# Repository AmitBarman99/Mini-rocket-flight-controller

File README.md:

# Mini-rocket-flight-controller
PCB board of mini rocket flight controller capable to store flight data

## The image of  this PCB board :point_down:

### If you want to use this,follow these steps....

1. Download the [kicad](https://www.kicad.org/) and install it.
2. clone this repository

```bash
 git clone https://github.com/AmitBarman99/Mini-rocket-flight-controller.git 
```

3. Open the files or folder and customize them.
4. You can use [JLC pcb](https://jlcpcb.com/) for PCB fabrication

## [click here](https://amitbarman99.github.io/Mini-rocket-flight-controller/) to see the PCB board in 3D environment

 Be patient, it takes time to load
 
  I got help from this :point_right:[Repository](https://github.com/easyw/vrm360) to setup this 3D visualization. You can see it.

  ```javascript
  
  if (isAwasome){
        return true;
  }
  ```

  ## All the best

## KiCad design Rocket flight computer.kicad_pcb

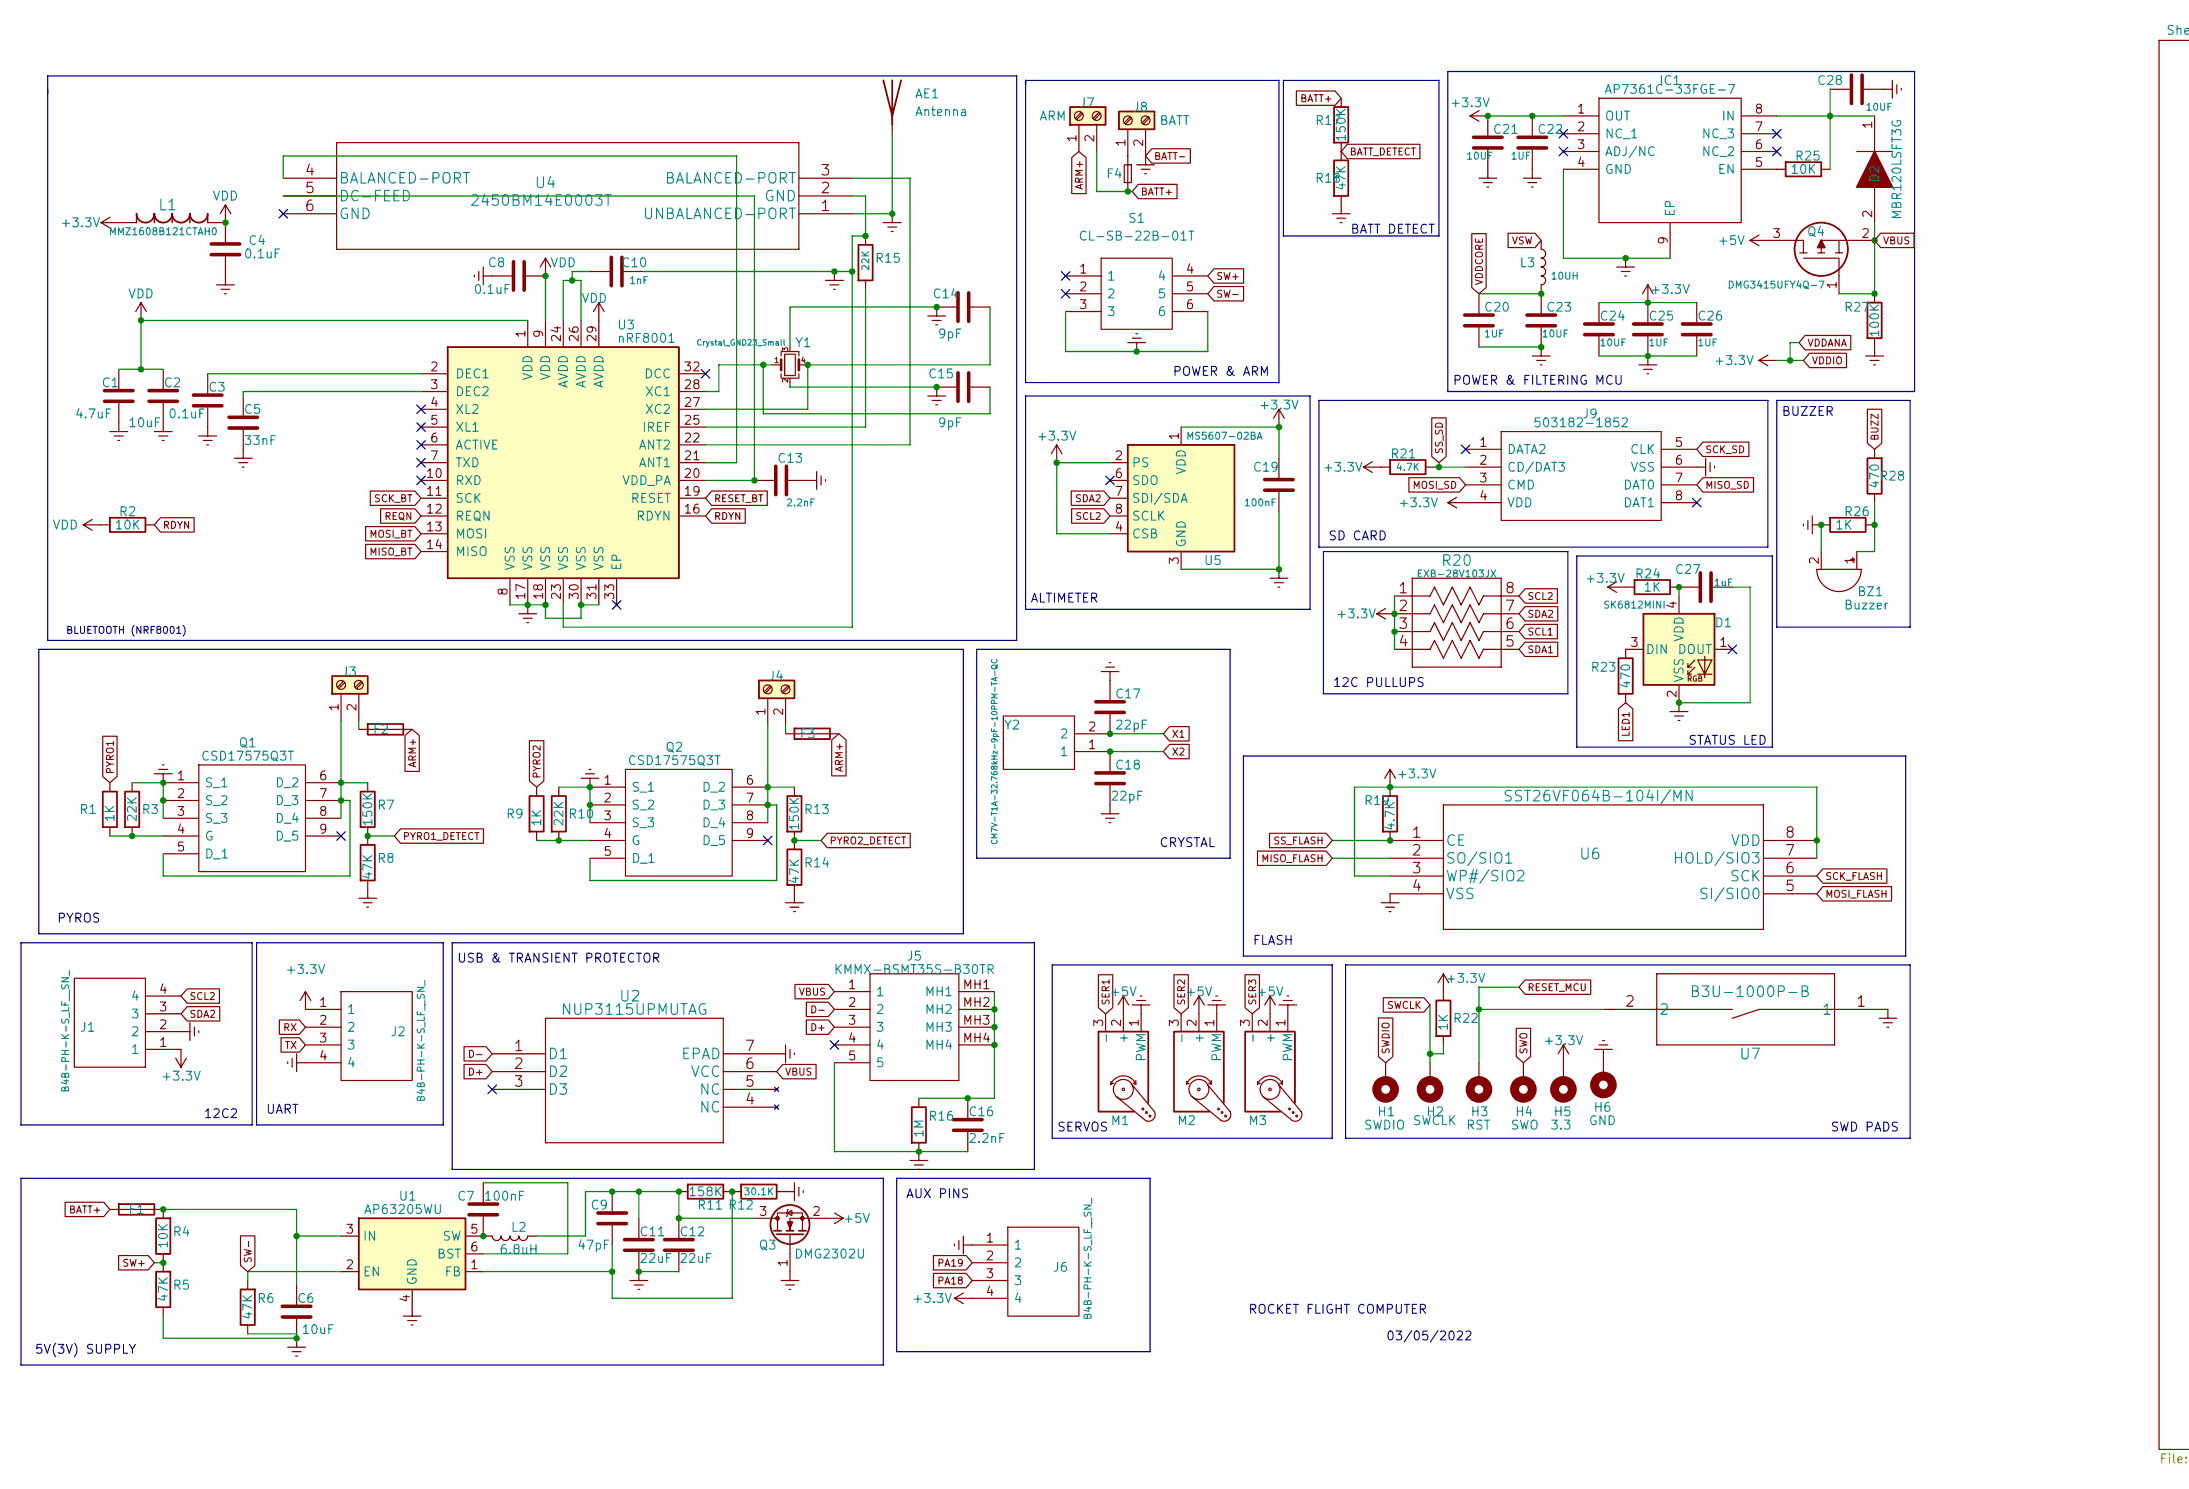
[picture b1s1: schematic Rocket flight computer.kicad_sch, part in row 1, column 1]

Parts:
AE1: Antenna; Banana_Jack_1Pin
BZ1: Buzzer; MagneticBuzzer_Kingstate_KCG0601
C1: 4.7uF; C_0201_0603Metric_Pad0.64x0.40mm_HandSolder
C2, C6: 10uF; C_0201_0603Metric_Pad0.64x0.40mm_HandSolder
C3, C4, C8: 0.1uF; C_0201_0603Metric_Pad0.64x0.40mm_HandSolder
C5: 33nF; C_0201_0603Metric_Pad0.64x0.40mm_HandSolder
C7, C19: 100nF; C_0201_0603Metric_Pad0.64x0.40mm_HandSolder
C9: 47pF; C_0201_0603Metric_Pad0.64x0.40mm_HandSolder
C10: 1nF; C_0201_0603Metric_Pad0.64x0.40mm_HandSolder
C11, C12: 22uF; C_0201_0603Metric_Pad0.64x0.40mm_HandSolder
C13, C16: 2.2nF; C_0201_0603Metric_Pad0.64x0.40mm_HandSolder
C14, C15: 9pF; C_0201_0603Metric_Pad0.64x0.40mm_HandSolder
C17, C18: 22pF; C_0201_0603Metric_Pad0.64x0.40mm_HandSolder
C20, C22, C25, C26: 1UF; C_0201_0603Metric_Pad0.64x0.40mm_HandSolder
C21, C23, C24, C28: 10UF; C_0201_0603Metric_Pad0.64x0.40mm_HandSolder
C27: 1uF; C_0201_0603Metric_Pad0.64x0.40mm_HandSolder
D1: SK6812MINI; LED_SK6812_PLCC4_5.0x5.0mm_P3.2mm
D2: MBR120LSFT3G; Manufacturer_Part_Number MBR120LSFT3G; Mouser Part Number 863-MBR120LSFT3G
F1, F2, F3: Fuse; Fuse_0402_1005Metric_Pad0.77x0.64mm_HandSolder
F4: Fuse_Small; SMA_Amphenol_132134-11_Vertical
H1: SWDIO; MountingHole_2.2mm_M2_Pad_Via
H2: SWCLK; MountingHole_2.2mm_M2_Pad_Via
H3: RST; MountingHole_2.2mm_M2_Pad_Via
H4: SWO; MountingHole_2.2mm_M2_Pad_Via
H5: 3.3; MountingHole_2.2mm_M2_Pad_Via
H6: GND; MountingHole_2.2mm_M2_Pad_Via
IC1: AP7361C-33FGE-7; Manufacturer_Part_Number AP7361C-33FGE-7; Mouser Part Number 621-AP7361C-33FGE-7
J1, J2, J6: B4B-PH-K-S_LF__SN_; B4B-PH-K-SLF_SN; Manufacturer_Part_Number B4B-PH-K-S(LF)(SN)
J3, J4, J7: ARM; Banana_Jack_2Pin
J5: KMMX-BSMT35S-B30TR; KMMXBSMT35SB30TR; Manufacturer_Part_Number KMMX-BSMT35S-B30TR; Mouser Part Number 806-KMMXBSMT35SB30TR
J8: BATT; TerminalBlock_TE_282834-2_1x02_P2.54mm_Horizontal
J9: 503182-1852; 5031821852; Manufacturer_Part_Number 503182-1852; Mouser Part Number 538-503182-1852
L1: MMZ1608B121CTAH0
L2: 6.8uH; L_0201_0603Metric_Pad0.64x0.40mm_HandSolder
L3: 10UH; L_0201_0603Metric_Pad0.64x0.40mm_HandSolder
M1, M2, M3: Motor_Servo; PinHeader_1x03_P2.54mm_Vertical_SMD_Pin1Left
Q1, Q2: CSD17575Q3T; Manufacturer_Part_Number CSD17575Q3T; Mouser Part Number 595-CSD17575Q3T
Q3: DMG2302U; SOT-23_Handsoldering
Q4: DMG3415UFY4Q-7; DMG3415UFY47; Manufacturer_Part_Number DMG3415UFY4Q-7; Mouser Part Number 621-DMG3415UFY4Q-7
R1, R9, R22, R24, R26: 1K; R_0201_0603Metric_Pad0.64x0.40mm_HandSolder
R2, R4, R25: 10K; R_0201_0603Metric_Pad0.64x0.40mm_HandSolder
R3, R10, R15: 22K; R_0201_0603Metric_Pad0.64x0.40mm_HandSolder
R5, R6, R8, R14, R18: 47K; R_0201_0603Metric_Pad0.64x0.40mm_HandSolder
R7, R13, R17: 150K; R_0201_0603Metric_Pad0.64x0.40mm_HandSolder
R11: 158K; R_0201_0603Metric_Pad0.64x0.40mm_HandSolder
R12: 30.1K; R_0201_0603Metric_Pad0.64x0.40mm_HandSolder
R16: 1M; R_0201_0603Metric_Pad0.64x0.40mm_HandSolder
R19, R21: 4.7K; R_0201_0603Metric_Pad0.64x0.40mm_HandSolder
R20: EXB-28V103JX
R23, R28: 470; R_0201_0603Metric_Pad0.64x0.40mm_HandSolder
R27: 100K; R_0201_0603Metric_Pad0.64x0.40mm_HandSolder
S1: CL-SB-22B-01T; CLSB22B01T; Manufacturer_Part_Number CL-SB-22B-01T
U1: AP63205WU; TSOT-23-6_HandSoldering
U2: NUP3115UPMUTAG
U3: nRF8001; QFN-32-1EP_5x5mm_P0.5mm_EP3.45x3.45mm
U4: 2450BM14E0003T
U5: MS5607-02BA; LGA-8_3x5mm_P1.25mm
U6: SST26VF064B-104I/MN; SST26VF064B-104IMN
U7: B3U-1000P-B
Y1: Crystal_GND23_Small; Crystal_SMD_2016-4Pin_2.0x1.6mm
Y2: CM7V-T1A-32.768kHz-9pF-10PPM-TA-QC; CM7V32768TBQA020; Manufacturer_Part_Number CM7V-T1A-32.768kHz-9pF-10PPM-TA-QC; Mouser Part Number 428-201565-MG01

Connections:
+5V: M1.2 (+), M2.2 (+), M3.2 (+), Q3.2 (S), Q4.3; also elsewhere on the board
ARM+: F2.1, F3.1, J7.1
BATT+: F1.2, F4.2, J7.2, R17.1
BATT-: AE1.1 (A), BZ1.2 (+), C1.2, C2.2, C3.2, C4.2, C5.2, C6.2, C8.2, C10.1, C11.2, C12.2, C13.1, C14.2, C15.2, C16.2, C17.1, C18.2, C19.2, C20.2, C21.2, C22.2, C23.2, C24.2, C25.2, C26.2, C27.1, C28.1, D1.2 (VSS), H6.1, IC1.4 (GND), IC1.9 (EP), J1.2, J2.4, J5.5, J6.1, J8.2, J9.6 (VSS), M1.1 (PWM), M2.1 (PWM), M3.1 (PWM), Q1.1 (S_1), Q1.2 (S_2), Q1.3 (S_3), Q2.1 (S_1), Q2.2 (S_2), Q2.3 (S_3), Q3.1 (G), R3.1, R5.1, R6.1, R8.2, R10.1, R12.1, R14.2, R15.1, R16.2, R18.2, R26.2, R27.2, S1.3, S1.6, U1.4 (GND), U2.7 (EPAD), U3.8 (VSS), U3.17 (VSS), U3.18 (VSS), U3.23 (VSS), U3.30 (VSS), U3.31 (VSS), U4.1 (UNBALANCED-PORT), U4.2 (GND), U5.3 (GND), U6.4 (VSS), U7.1, Y1.2, Y1.3; also elsewhere on the board
BATT_DETECT: R17.2, R18.1; also elsewhere on the board
BUZZ: R28.2; also elsewhere on the board
D+: J5.3, U2.2 (D2); also elsewhere on the board
D-: J5.2, U2.1 (D1); also elsewhere on the board
LED1: R23.2; also elsewhere on the board
MISO_BT: U3.14 (MISO); also elsewhere on the board
MISO_FLASH: U6.2 (SO/SIO1); also elsewhere on the board
MISO_SD: J9.7 (DAT0); also elsewhere on the board
MOSI_BT: U3.13 (MOSI); also elsewhere on the board
MOSI_FLASH: U6.5 (SI/SIO0); also elsewhere on the board
MOSI_SD: J9.3 (CMD); also elsewhere on the board
unnamed: BZ1.1 (-), R26.1, R28.1
unnamed: C3.1, U3.2 (DEC1)
unnamed: C5.1, U3.3 (DEC2)
unnamed: C6.1, F1.1, R4.2, U1.3 (IN)
unnamed: C7.1, U1.6 (BST)
unnamed: C7.2, L2.2, U1.5 (SW)
unnamed: C9.2, R11.1, R12.2, U1.1 (FB)
unnamed: C10.2, U3.24 (AVDD), U3.26 (AVDD)
unnamed: C9.1, C11.1, C12.1, L2.1, Q3.3 (D), R11.2
unnamed: C13.2, U3.20 (VDD_PA), U4.5 (DC-FEED)
unnamed: C14.1, U3.27 (XC2), Y1.4
unnamed: C15.1, U3.28 (XC1), Y1.1
unnamed: C16.1, J5.MH1, J5.MH2, J5.MH3, J5.MH4, R16.1
unnamed: C27.2, D1.4 (VDD), R24.1
unnamed: C28.2, D2.1, IC1.8 (IN), R25.1
unnamed: D1.3 (DIN), R23.1
unnamed: F2.2, J3.2
unnamed: F3.2, J4.2
unnamed: F4.1, J8.1
unnamed: IC1.5 (EN), R25.2
unnamed: J3.1, Q1.5 (D_1), Q1.6 (D_2), Q1.7 (D_3), Q1.8 (D_4), R7.1
unnamed: J4.1, Q2.5 (D_1), Q2.6 (D_2), Q2.7 (D_3), Q2.8 (D_4), R13.1
unnamed: Q1.4 (G), R1.2, R3.2
unnamed: Q2.4 (G), R9.2, R10.2
unnamed: R15.2, U3.25 (IREF)
unnamed: U3.21 (ANT1), U4.4 (BALANCED-PORT)
unnamed: U3.22 (ANT2), U4.3 (BALANCED-PORT)
PA18: J6.3; also elsewhere on the board
PA19: J6.2; also elsewhere on the board
PYRO1: R1.1; also elsewhere on the board
PYRO1_DETECT: R7.2, R8.1; also elsewhere on the board
PYRO2: R9.1; also elsewhere on the board
PYRO2_DETECT: R13.2, R14.1; also elsewhere on the board
RDYN: R2.1, U3.16 (RDYN); also elsewhere on the board
REQN: U3.12 (REQN); also elsewhere on the board
RESET_BT: U3.19 (RESET); also elsewhere on the board
RESET_MCU: H3.1, U7.2; also elsewhere on the board
RX: J2.2; also elsewhere on the board
SCK_BT: U3.11 (SCK); also elsewhere on the board
SCK_FLASH: U6.6 (SCK); also elsewhere on the board
SCK_SD: J9.5 (CLK); also elsewhere on the board
SCL1: R20.6; also elsewhere on the board
SCL2: J1.4, R20.8, U5.8 (SCLK); also elsewhere on the board
SDA1: R20.5; also elsewhere on the board
SDA2: J1.3, R20.7, U5.7 (SDI/SDA); also elsewhere on the board
SER1: M1.3 (-); also elsewhere on the board
SER2: M2.3 (-); also elsewhere on the board
SER3: M3.3 (-); also elsewhere on the board
SS_FLASH: R19.2, U6.1 (CE); also elsewhere on the board
SS_SD: J9.2 (CD/DAT3), R21.1; also elsewhere on the board
SW+: R4.1, R5.2, S1.4
SW-: R6.2, S1.5, U1.2 (EN)
SWCLK: H2.1, R22.2; also elsewhere on the board
SWDIO: H1.1; also elsewhere on the board
SWO: H4.1; also elsewhere on the board
TX: J2.3; also elsewhere on the board
VBUS: D2.2, J5.1, Q4.1, Q4.2, R27.1, U2.6 (VCC)
VDD: C1.1, C2.1, C4.1, C8.1, L1.1, R2.2, U3.1 (VDD), U3.9 (VDD), U3.29 (AVDD)
VDDANA: C19.1, C21.1, C22.1, C24.1, C25.1, C26.1, H5.1, IC1.1 (OUT), J1.1, J2.1, J6.4, J9.4 (VDD), L1.2, R19.1, R20.1, R20.2, R20.3, R20.4, R21.2, R22.1, R24.2, U5.1 (VDD), U5.2 (PS), U5.4 (CSB), U5.5 (CSB), U6.3 (WP#/SIO2), U6.7 (HOLD/SIO3), U6.8 (VDD); also elsewhere on the board
VDDCORE: C20.1, C23.1, L3.2; also elsewhere on the board
VSW: L3.1; also elsewhere on the board
X1: C17.2, Y2.2; also elsewhere on the board
X2: C18.1, Y2.1; also elsewhere on the board

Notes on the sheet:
POWER & ARM
AUX PINS
FLASH
USB & TRANSIENT PROTECTOR
SWD PADS
BATT DETECT
BUZZER
SD CARD
PYROS
UART
5V(3V) SUPPLY
STATUS LED
BLUETOOTH (NRF8001)
03/05/2022
ROCKET FLIGHT COMPUTER
SERVOS
CRYSTAL
ALTIMETER
12C2
12C PULLUPS
POWER & FILTERING MCU

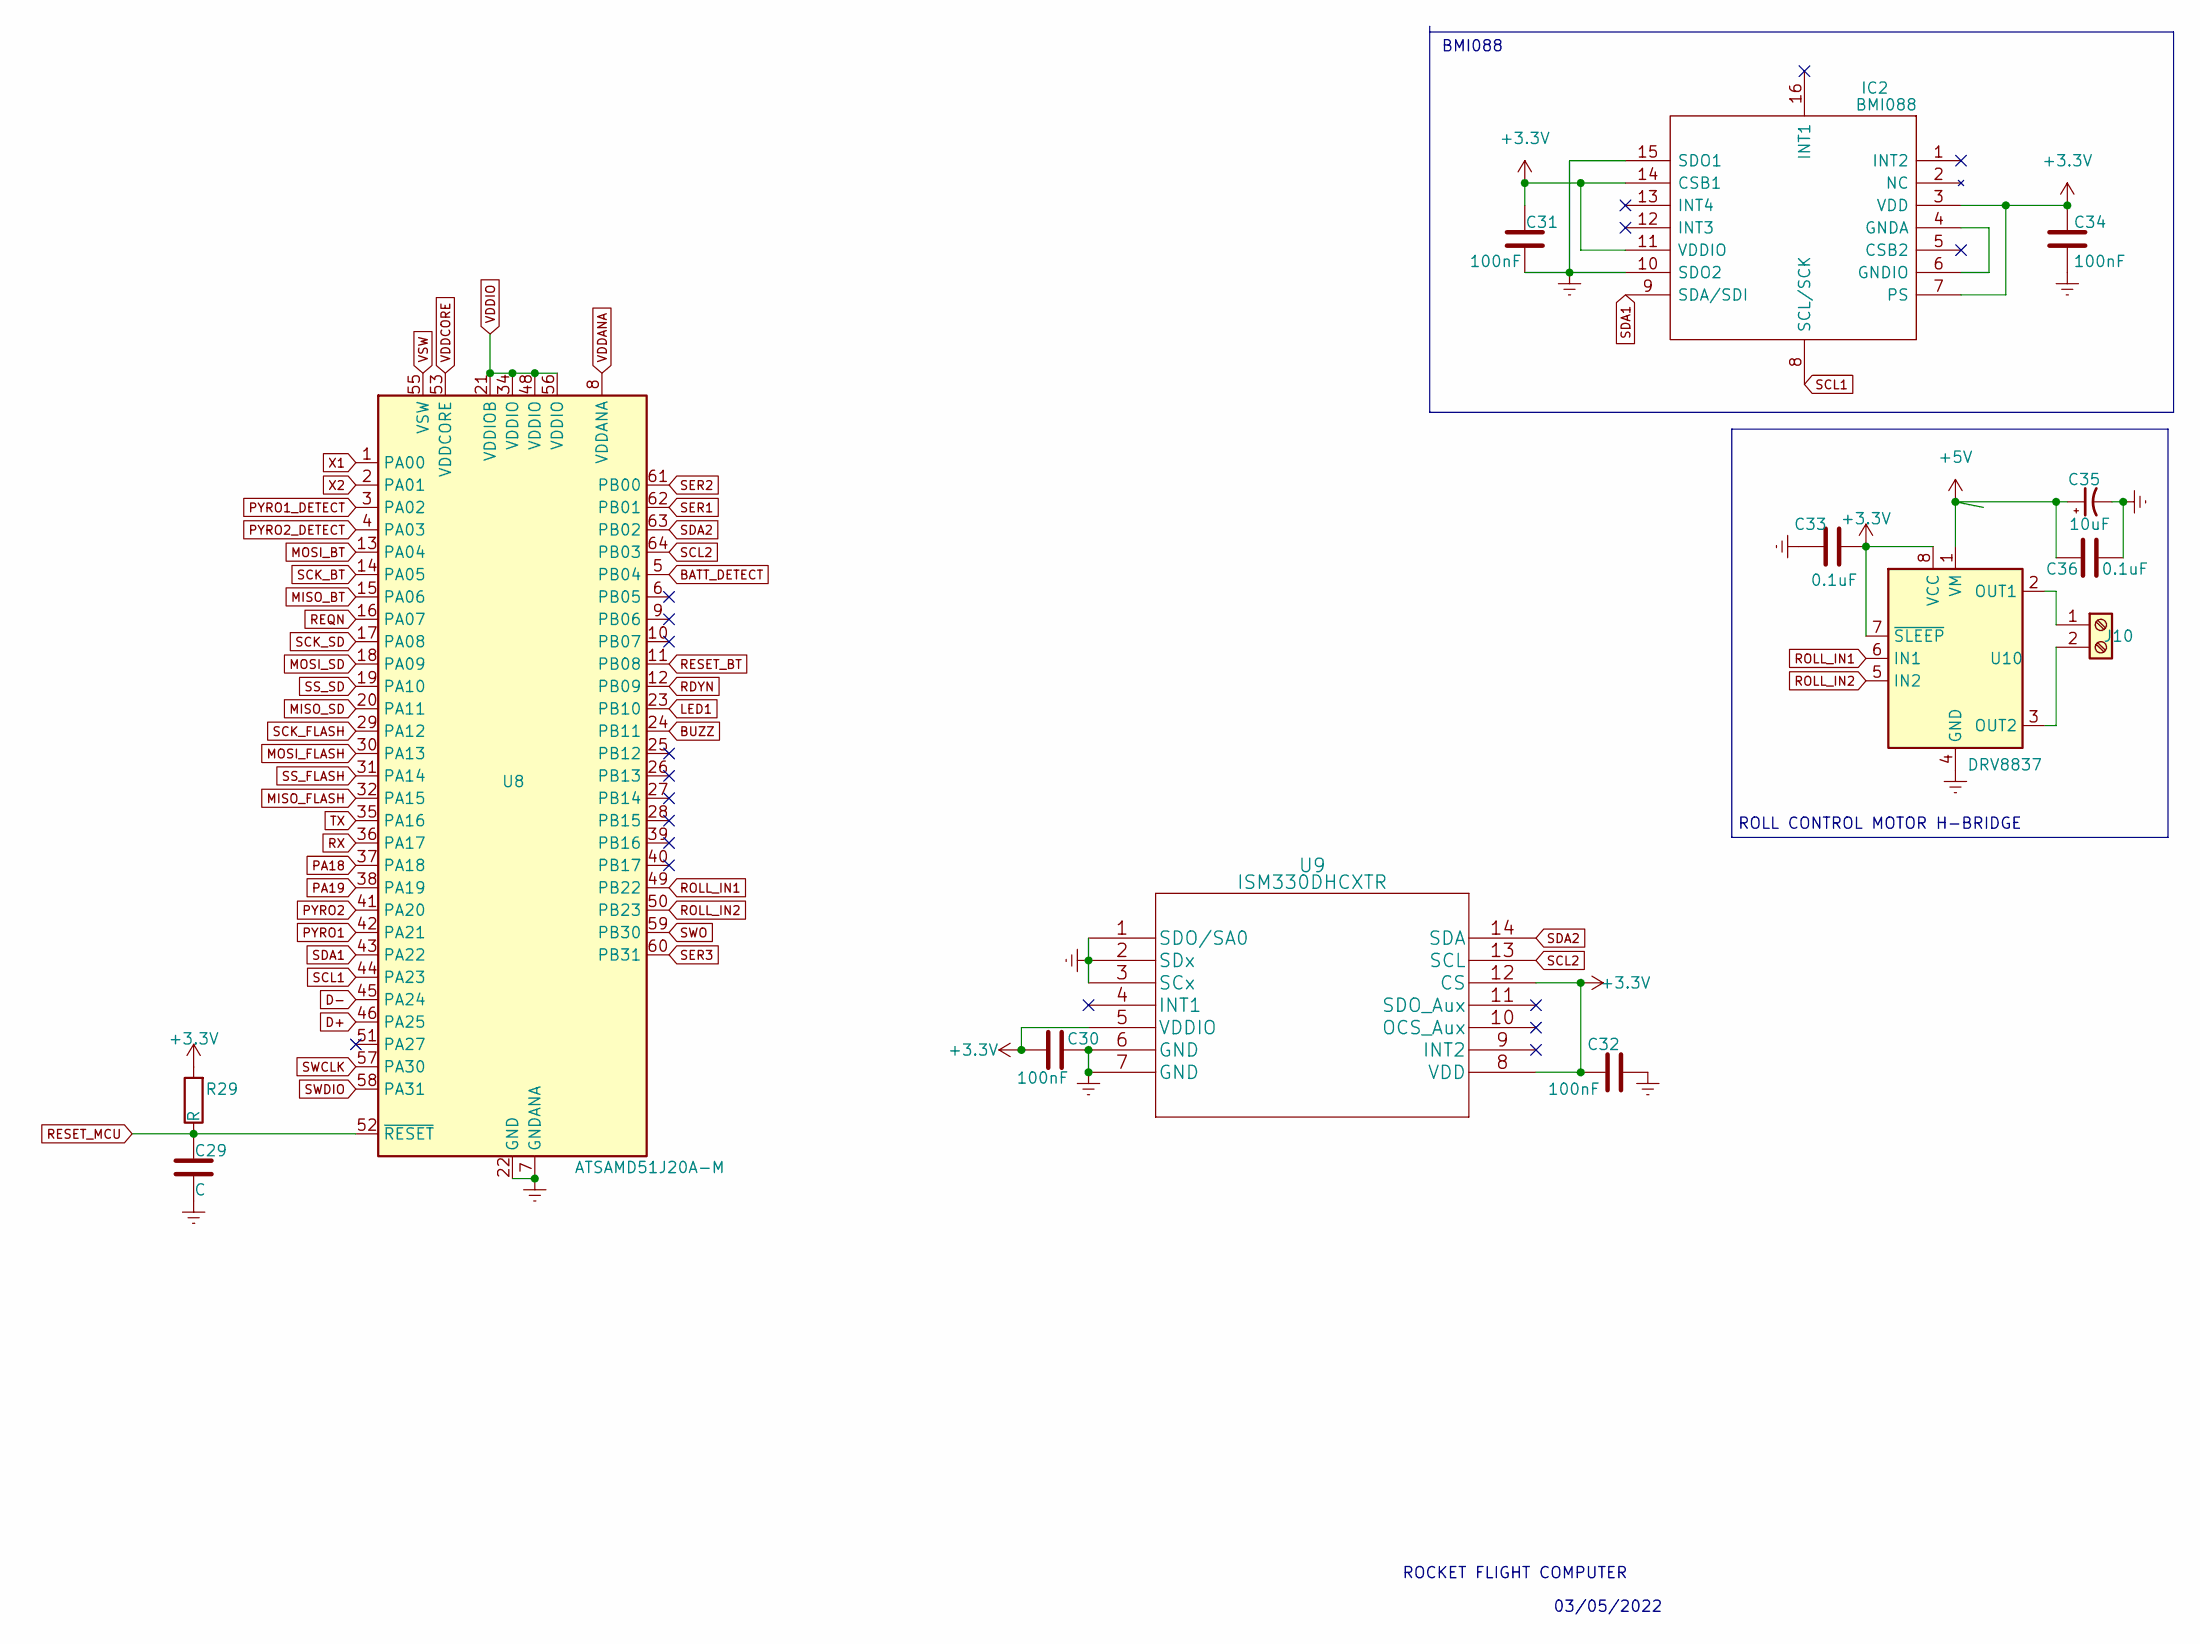
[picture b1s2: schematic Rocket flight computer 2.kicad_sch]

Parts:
C29: C; C_0201_0603Metric_Pad0.64x0.40mm_HandSolder
C30, C31, C32, C34: 100nF; C_0201_0603Metric_Pad0.64x0.40mm_HandSolder
C33, C36: 0.1uF; C_0201_0603Metric_Pad0.64x0.40mm_HandSolder
C35: 10uF; CP_EIA-1608-08_AVX-J_Pad1.25x1.05mm_HandSolder
IC2: BMI088; Manufacturer_Part_Number BMI088; Mouser Part Number 262-BMI088
J10: ARM; Banana_Jack_2Pin
R29: R; R_0201_0603Metric_Pad0.64x0.40mm_HandSolder
U8: ATSAMD51J20A-M; QFN-64-1EP_9x9mm_P0.5mm_EP3.8x3.8mm
U9: ISM330DHCXTR
U10: DRV8837; WSON-8-1EP_2x2mm_P0.5mm_EP0.9x1.6mm_ThermalVias

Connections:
+5V: C35.1, C36.2, U10.1 (VM); also elsewhere on the board
BATT-: C29.1, C30.1, C31.2, C32.1, C33.2, C34.2, C35.2, C36.1, IC2.10 (SDO2), IC2.15 (SDO1), U8.7 (GNDANA), U8.22 (GND), U8.33 (GND), U8.47 (GND), U8.54 (GND), U8.65 (GND), U9.1 (SDO/SA0), U9.2 (SDx), U9.3 (SCx), U9.6 (GND), U9.7 (GND), U10.4 (GND), U10.9 (GND); also elsewhere on the board
BATT_DETECT: U8.5 (PB04); also elsewhere on the board
BUZZ: U8.24 (PB11); also elsewhere on the board
D+: U8.46 (PA25); also elsewhere on the board
D-: U8.45 (PA24); also elsewhere on the board
LED1: U8.23 (PB10); also elsewhere on the board
MISO_BT: U8.15 (PA06); also elsewhere on the board
MISO_FLASH: U8.32 (PA15); also elsewhere on the board
MISO_SD: U8.20 (PA11); also elsewhere on the board
MOSI_BT: U8.13 (PA04); also elsewhere on the board
MOSI_FLASH: U8.30 (PA13); also elsewhere on the board
MOSI_SD: U8.18 (PA09); also elsewhere on the board
unnamed: IC2.4 (GNDA), IC2.6 (GNDIO)
unnamed: J10.1, U10.2 (OUT1)
unnamed: J10.2, U10.3 (OUT2)
PA18: U8.37 (PA18); also elsewhere on the board
PA19: U8.38 (PA19); also elsewhere on the board
PYRO1: U8.42 (PA21); also elsewhere on the board
PYRO1_DETECT: U8.3 (PA02); also elsewhere on the board
PYRO2: U8.41 (PA20); also elsewhere on the board
PYRO2_DETECT: U8.4 (PA03); also elsewhere on the board
RDYN: U8.12 (PB09); also elsewhere on the board
REQN: U8.16 (PA07); also elsewhere on the board
RESET_BT: U8.11 (PB08); also elsewhere on the board
RESET_MCU: C29.2, R29.1, U8.52 (~RESET); also elsewhere on the board
ROLL_IN1: U8.49 (PB22), U10.6 (IN1)
ROLL_IN2: U8.50 (PB23), U10.5 (IN2)
RX: U8.36 (PA17); also elsewhere on the board
SCK_BT: U8.14 (PA05); also elsewhere on the board
SCK_FLASH: U8.29 (PA12); also elsewhere on the board
SCK_SD: U8.17 (PA08); also elsewhere on the board
SCL1: IC2.8 (SCL/SCK), U8.44 (PA23); also elsewhere on the board
SCL2: U8.64 (PB03), U9.13 (SCL); also elsewhere on the board
SDA1: IC2.9 (SDA/SDI), U8.43 (PA22); also elsewhere on the board
SDA2: U8.63 (PB02), U9.14 (SDA); also elsewhere on the board
SER1: U8.62 (PB01); also elsewhere on the board
SER2: U8.61 (PB00); also elsewhere on the board
SER3: U8.60 (PB31); also elsewhere on the board
SS_FLASH: U8.31 (PA14); also elsewhere on the board
SS_SD: U8.19 (PA10); also elsewhere on the board
SWCLK: U8.57 (PA30); also elsewhere on the board
SWDIO: U8.58 (PA31); also elsewhere on the board
SWO: U8.59 (PB30); also elsewhere on the board
TX: U8.35 (PA16); also elsewhere on the board
VDDANA: C30.2, C31.1, C32.2, C33.1, C34.1, IC2.3 (VDD), IC2.7 (PS), IC2.11 (VDDIO), IC2.14 (CSB1), R29.2, U8.8 (VDDANA), U8.21 (VDDIOB), U8.34 (VDDIO), U8.48 (VDDIO), U8.56 (VDDIO), U9.5 (VDDIO), U9.8 (VDD), U9.12 (CS), U10.7 (~SLEEP), U10.8 (VCC); also elsewhere on the board
VDDCORE: U8.53 (VDDCORE); also elsewhere on the board
VSW: U8.55 (VSW); also elsewhere on the board
X1: U8.1 (PA00); also elsewhere on the board
X2: U8.2 (PA01); also elsewhere on the board

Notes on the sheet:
03/05/2022
BMI088
ROLL CONTROL MOTOR H-BRIDGE
ROCKET FLIGHT COMPUTER

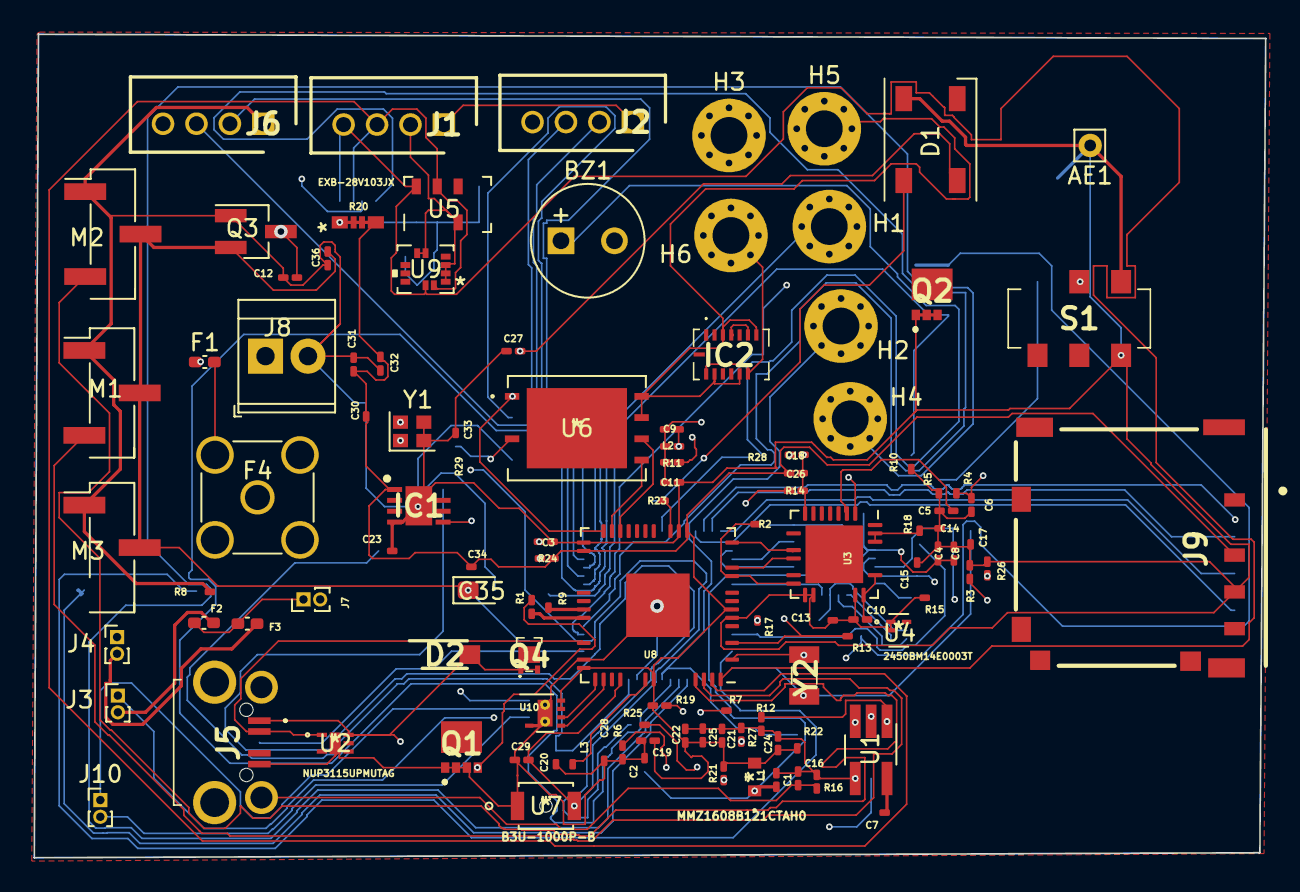
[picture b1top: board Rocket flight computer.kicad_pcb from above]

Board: 4 copper layers, 73.6 x 49.2 mm, 114 parts (0 on the bottom side), 83 nets.

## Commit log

2022-06-21 Create README.md
    additional info. of this projects

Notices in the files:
parts and their libraries:
Copyright 2021 Accelerated Designs. All rights reserved.
